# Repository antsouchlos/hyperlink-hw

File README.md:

# HyperLink

A PCB for gathering data form CommonSense boards over bluetooth and
retransmitting over wifi.

After cloning, the libraries can be downloaded using

```bash
$ git submodule update --init
```

## PCB

## Schematic

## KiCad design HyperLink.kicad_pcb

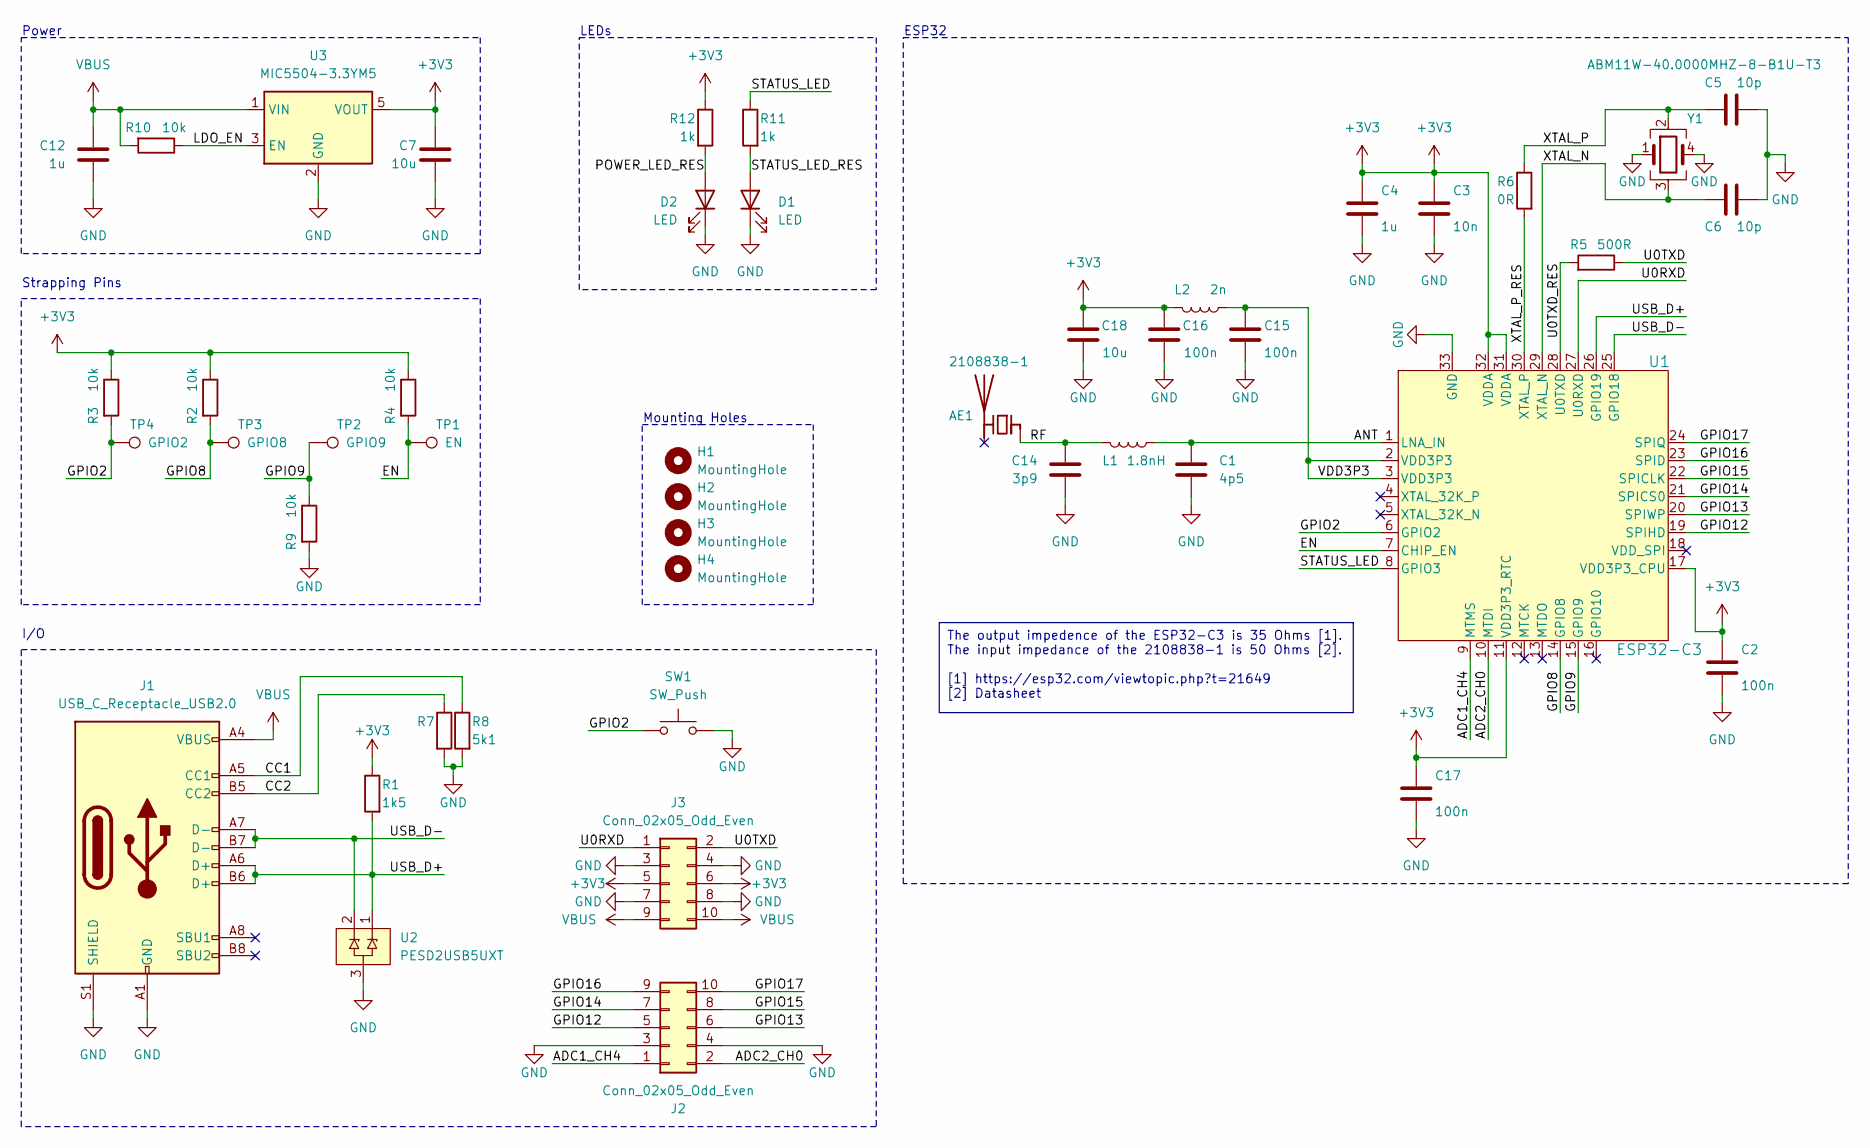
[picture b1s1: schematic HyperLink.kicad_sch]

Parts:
AE1: 2108838-1
C1: 4p5; C_0402_1005Metric
C2, C15, C16, C17: 100n; C_0402_1005Metric
C3: 10n; C_0402_1005Metric
C4, C12: 1u; C_0402_1005Metric
C5, C6: 10p; C_0402_1005Metric
C7, C18: 10u; C_0603_1608Metric
C14: 3p9; C_0402_1005Metric
D1, D2: LED; LED_0603_1608Metric
H1, H2, H3, H4: MountingHole; MountingHole_2.2mm_M2
J1: USB_C_Receptacle_USB2.0; USB4105-GF-A
J2, J3: Conn_02x05_Odd_Even; PinHeader_2x05_P2.54mm_Vertical
L1: 1.8nH; L_0402_1005Metric
L2: 2n; L_0402_1005Metric
R1: 1k5; R_0402_1005Metric
R2, R3, R4, R9, R10: 10k; R_0402_1005Metric
R5: 500R; R_0402_1005Metric
R6: 0R; R_0402_1005Metric
R7, R8: 5k1; R_0402_1005Metric
R11, R12: 1k; R_0402_1005Metric
SW1: SW_Push; SW_SPST_B3U-1000P
TP1: EN; TestPoint_Pad_D1.5mm
TP2: GPIO9; TestPoint_Pad_D1.5mm
TP3: GPIO8; TestPoint_Pad_D1.5mm
TP4: GPIO2; TestPoint_Pad_D1.5mm
U1: ESP32-C3; QFN32_5X5_EXP
U2: PESD2USB5UXT; TSOT-23
U3: MIC5504-3.3YM5; SOT-23-5
Y1: ABM11W-40.0000MHZ-8-B1U-T3; ABM11W-30.0000MHZ-7-D1X-T3

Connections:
+3V3: C2.1, C3.1, C4.1, C7.1, C16.1, C17.1, C18.1, J3.5, J3.6, L2.1, R1.1, R2.1, R3.1, R4.1, R12.1, U1.11 (VDD3P3_RTC), U1.17 (VDD3P3_CPU), U1.31 (VDDA), U1.32 (VDDA), U3.5 (VOUT)
/ADC1_CH4: J2.1, U1.9 (MTMS)
/ADC2_CH0: J2.2, U1.10 (MTDI)
/ANT: C1.1, L1.2, U1.1 (LNA_IN)
/CC1: J1.A5 (CC1), R8.1
/CC2: J1.B5 (CC2), R7.1
/EN: R4.2, TP1.1, U1.7 (CHIP_EN)
/GPIO2: R3.2, SW1.2, TP4.1, U1.6 (GPIO2)
/GPIO8: R2.2, TP3.1, U1.14 (GPIO8)
/GPIO9: R9.1, TP2.1, U1.15 (GPIO9)
/GPIO12: J2.5, U1.19 (SPIHD)
/GPIO13: J2.6, U1.20 (SPIWP)
/GPIO14: J2.7, U1.21 (SPICS0)
/GPIO15: J2.8, U1.22 (SPICLK)
/GPIO16: J2.9, U1.23 (SPID)
/GPIO17: J2.10, U1.24 (SPIQ)
/LDO_EN: R10.1, U3.3 (EN)
/POWER_LED_RES: D2.2 (A), R12.2
/RF: AE1.1 (FEED), C14.1, L1.1
/STATUS_LED: R11.1, U1.8 (GPIO3)
/STATUS_LED_RES: D1.2 (A), R11.2
/U0RXD: J3.1, U1.27 (U0RXD)
/U0TXD: J3.2, R5.1
/U0TXD_RES: R5.2, U1.28 (U0TXD)
/USB_D+: J1.A6 (D+), J1.B6 (D+), R1.2, U1.26 (GPIO19), U2.1
/USB_D-: J1.A7 (D-), J1.B7 (D-), U1.25 (GPIO18), U2.2
/VDD3P3: C15.1, L2.2, U1.2 (VDD3P3), U1.3 (VDD3P3)
/XTAL_N: C6.1, U1.29 (XTAL_N), Y1.3
/XTAL_P: C5.1, R6.1, Y1.2
/XTAL_P_RES: R6.2, U1.30 (XTAL_P)
GND: C1.2, C2.2, C3.2, C4.2, C5.2, C6.2, C7.2, C12.2, C14.2, C15.2, C16.2, C17.2, C18.2, D1.1 (K), D2.1 (K), J1.A1 (GND), J1.A12 (GND), J1.B1 (GND), J1.B12 (GND), J1.S1 (SHIELD), J2.3, J2.4, J3.3, J3.4, J3.7, J3.8, R7.2, R8.2, R9.2, SW1.1, U1.33 (GND), U2.3, U3.2 (GND), Y1.1, Y1.4
VBUS: C12.1, J1.A4 (VBUS), J1.A9 (VBUS), J1.B4 (VBUS), J1.B9 (VBUS), J3.9, J3.10, R10.2, U3.1 (VIN)

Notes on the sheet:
The output impedence of the ESP32-C3 is 35 Ohms [1]. The input impedance of the 2108838-1 is 50 Ohms [2]. [1] https://esp32.com/viewtopic.php?t=21649 [2] Datasheet
ESP32
I/O
Mounting Holes
Power
Strapping Pins
LEDs

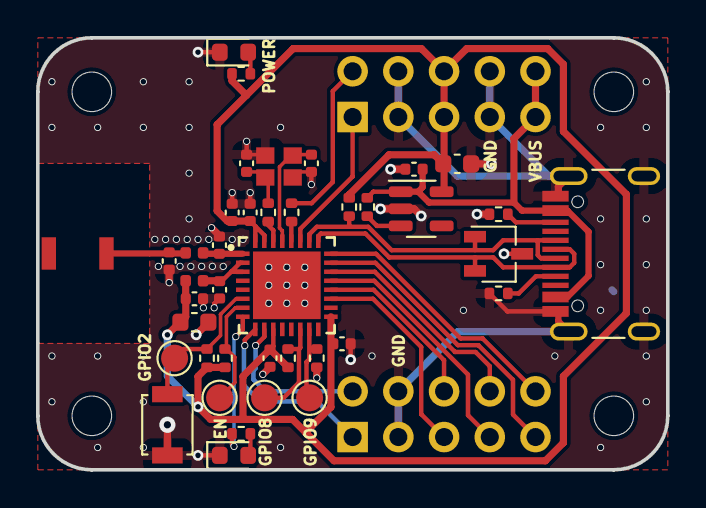
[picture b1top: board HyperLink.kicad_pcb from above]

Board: 2 copper layers, 35.0 x 24.0 mm, 46 parts (0 on the bottom side), 32 nets.

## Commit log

2023-08-02 Copy stuff from other pc
2023-08-03 Add gitignore; Route USB lines
2023-08-03 Update to newer version of encyclopedia galactica
2023-08-07 Design first version of board (Crystal not routed yet)
2023-08-07 Remove board name; Minor other changes
2023-08-07 Add button; Move power lines
2023-08-07 Move shield resistor and cap to front
2023-08-07 Connect Crystal; Add 500R resistor to U0TXD
2023-08-07 Connect all shield pads
2023-08-07 Add via stitching
2023-08-07 Add USB pullups/downs and clean up schematic
2023-08-07 Add USB resistors to PCB
2023-08-09 Rename project
2023-08-09 Add TODOs to schematic
2023-08-22 Add README.md
2023-08-22 Update version of lib
2023-08-22 Replace LDO and add USB TVS diode
2023-08-22 Add status LEDs
2023-08-22 Clean up schematic
2023-08-22 Not sure what changed
2023-08-22 Tie SHIELD directly to GND
2023-08-22 Fix last remaining TODOs and clean up schematic
2023-08-22 Replace Antenna symbol with chip antenna
2023-08-22 Safety commit
2023-08-26 Remove 'F' from capacitor values
2023-09-13 Flip D+ and D- at connector
2023-09-13 Change connector thermal reliefs, various vias
2023-09-13 Check out new version of encyclopedia
2023-09-13 Update crystal footprint
2023-09-13 Replace unnecessarily thick traces with thinner ones
2023-09-13 Move status LED
2023-09-13 Add silk screen text
2023-09-13 Check out new version of library and replace usb connector footprint
2023-11-18 Change cap values
2023-11-21 Fix matching network component values
2024-02-23 Add pulldown resistor to GPIO9 pin
2024-10-20 Add doc generation workflow
2024-10-20 Fix doc generation workflow (#1)
    Reviewed-on: https://git.mercurial-manifold.eu/an.tsouchlos/hyperlink-hw/pulls/1
    Co-committed-by: Andreas Tsouchlos <an.tsouchlos@gmail.com>
2024-10-20 Add MIT license (#2)
    Reviewed-on: https://git.mercurial-manifold.eu/an.tsouchlos/hyperlink-hw/pulls/2
    Co-committed-by: Andreas Tsouchlos <an.tsouchlos@gmail.com>
2024-10-20 Change phrasing in README (#3)
    Reviewed-on: https://git.mercurial-manifold.eu/an.tsouchlos/hyperlink-hw/pulls/3
    Co-committed-by: Andreas Tsouchlos <an.tsouchlos@gmail.com>
